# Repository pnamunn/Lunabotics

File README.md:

# NASA Lunabotics 2024 Competition - Team ARES for SDSU

## Distros used:
Using Ubuntu 20.04 LTS on Jetson & Ubuntu 22.04 LTS on laptop.  ROS2 foxy on Jetson & ROS2 humble on laptop.  Different ROS2 versions shouldn't affect their ability to work together over a network.  
Python packages needed for controls:  rclpy, pyserial, sensor_msgs, bitarray  
Python packages needed for modified Vulcan video stream:  cv2, pyrealsense2, flask, numpy  

## Rover telecoms set up:
Ensure laptop & Jetson are both connected to the ARES_WAP

`ros2 run joy joy_node` on laptop to detect Logitech controller

`minicom -D /dev/<arduino_USB_port> -b 500000` on Jetson to serial monitor the Arduino Mega

`python3 serial_joystick.py` on Jetson

<run vulcan video stream on Jetson command>

<connect to appropriate IP address to view video stream on laptop>

## Passwords:
| Device              | Username | Password        |                         |
| :-----------------: | :------: | :-------------: | :---------------------: |
| Laptop              | steui    | WARHAWK         |                         |
| Jetson              | stubert  | S2P@C619        |                         |
| WAP connection      | ARES_WAP | 72878781        |                         |
| WAP config settings | admin    | DoctorShaffar<3 | Website: tplinkwifi.net |

## On Arduino Mega hat:
J17 connects to PB6 (drivetrain R) & PB5(drivetrain L)  
J18 connects to DH3 (exc tilt) & PL4 (depo tilt)  
J19 connects to DH5 (exc height) & PH4 (exc chain)  

## Logitech controller buttons mapping:
| Control        | Use                              |
| -------------: | :------------------------------  |
| Left joystick  | Drivetrain controls              |
| Right joystick | Camera gimble controls           |
| B or X         | Excavation chain fwd or backward |
| Y or A         | Excavation frame move up or down |
| LB or LT       | Depo bin tilt out or in          |
| RB or RT       | Excavation frame tilt out or in  |

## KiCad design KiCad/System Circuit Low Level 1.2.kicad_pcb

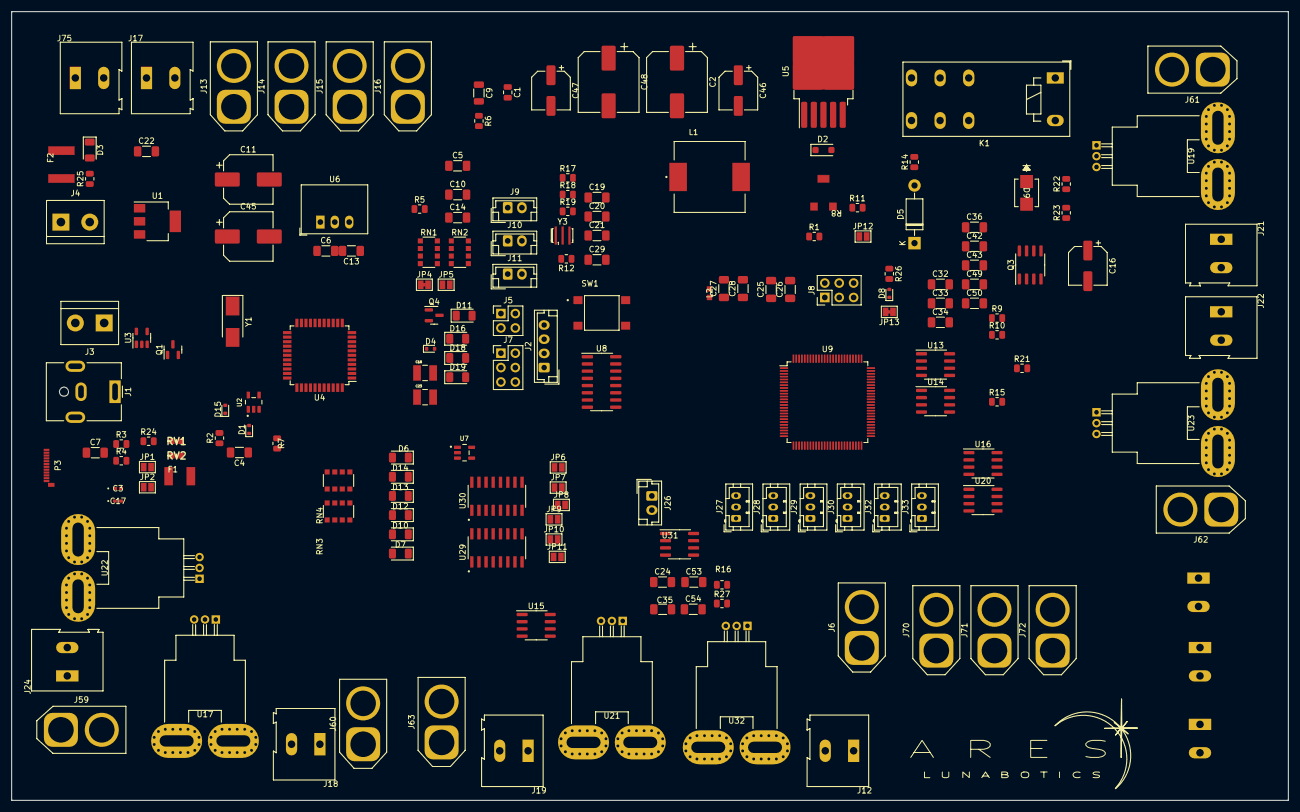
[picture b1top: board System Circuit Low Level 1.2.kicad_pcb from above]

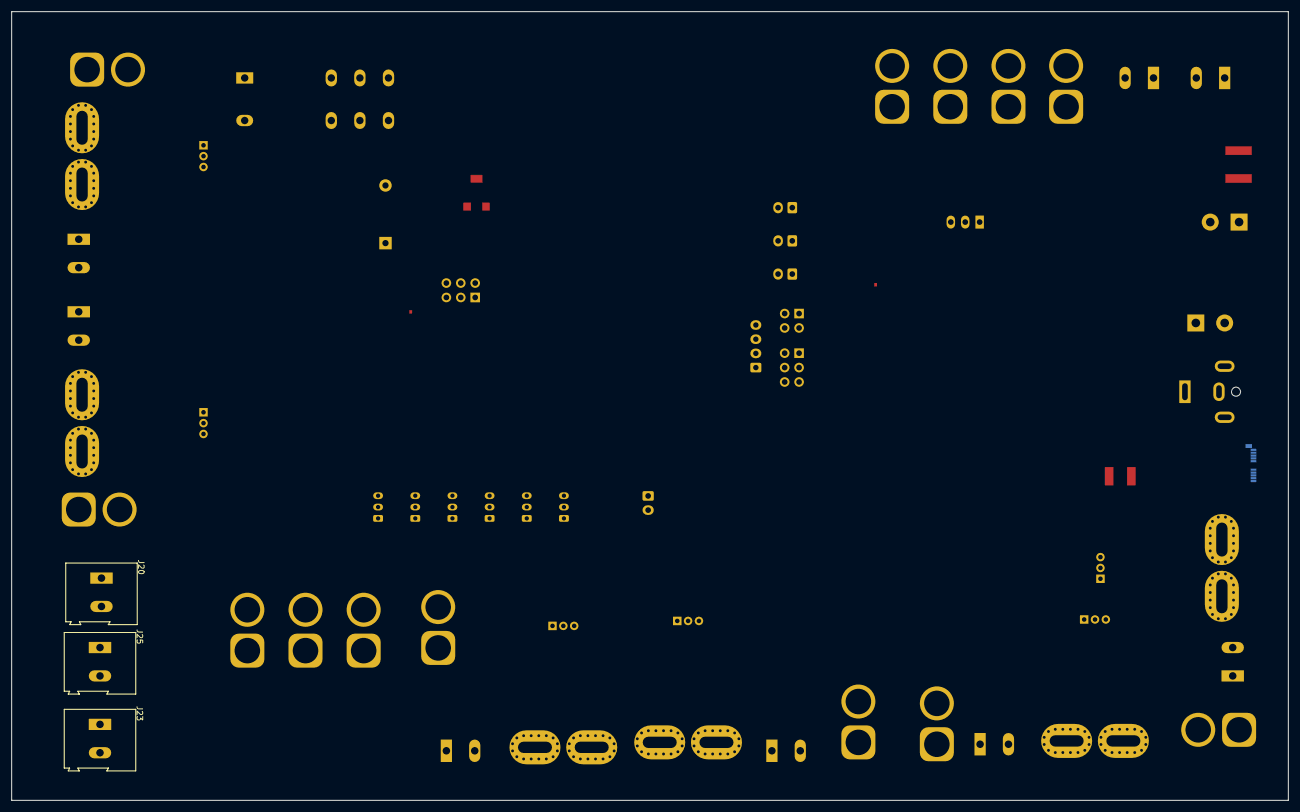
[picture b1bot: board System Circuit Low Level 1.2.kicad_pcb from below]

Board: 2 copper layers, 225.0 x 139.0 mm, 178 parts (3 on the bottom side), 121 nets, no tracks yet.

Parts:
C1: 100n; C_0805_2012Metric
C2, C48: 100u; CP_Elec_10x10.5
C3, C17: 22p; CAP_GCM155_MUR
C4, C5, C7, C10, C13, C14, C19, C21, C22, C24, C25, C26, C27, C28, C29, C32, C33, C34, C35, C36: 0.1u; C_1206_3216Metric_Pad1.33x1.80mm_HandSolder
C6: 0.33u; C_1206_3216Metric_Pad1.33x1.80mm_HandSolder
C9: 330p; C_1206_3216Metric
C11, C45: 47u; CP_Elec_8x10.5
C16, C46, C47: 10u; CP_Elec_6.3x5.8
C18, C23: 10u; CAPC3225X270N
C20: 0.022u; C_1206_3216Metric_Pad1.33x1.80mm_HandSolder
C42, C43, C49, C50, C53, C54: 10n; C_1206_3216Metric_Pad1.33x1.80mm_HandSolder
D1, D4, D8, D15: 1N4148WT; D_SOD-523
D2: MBR1020VL; D_SOD-123F
D3, D6, D7, D10, D11, D12, D13, D14, D16, D18, D19: LED; LED_1206_3216Metric
D5: 1N5819; D_DO-41_SOD81_P10.16mm_Horizontal
D9: 3A100Vstd; SMB_STM
F1: FuseF-MSMF050-2; FuseF-MSMF050-2-sty1
F2: 3A_tr 1.5A_hld Slow Burn; MF-SMDF
J1: Barrel_Jack_Switch; BarrelJack_CUI_PJ-063AH_Horizontal
J2: Conn_01x04; JST_EH_B4B-EH-A_1x04_P2.50mm_Vertical
J3, J4: Screw_Terminal_01x02; TerminalBlock_bornier-2_P5.08mm
J5: Conn_02x02_Odd_Even; PinHeader_2x02_P2.54mm_Vertical
J6, J13, J14, J15, J16, J59, J60, J61, J62, J63, J70, J71, J72: XT-90F-vert; AMASS_XT60-F_1x02_P7.20mm_Vertical
J7, J8: Conn_02x03_Odd_Even; PinHeader_2x03_P2.54mm_Vertical
J9, J10, J11, J26: Conn_01x02; JST_EH_B2B-EH-A_1x02_P2.50mm_Vertical
J12, J17, J18, J19, J20, J21, J22, J23, J24, J25, J75: Screw_Terminal_01x02; TerminalBlock_Altech_AK300-2_P5.00mm
J27, J28, J29, J30, J32, J33: Conn_01x03; JST_PH_B3B-PH-K_1x03_P2.00mm_Vertical
JP1, JP2, JP5, JP6, JP7, JP8, JP9, JP10, JP11, JP12: SolderJumper_2_Open; SolderJumper-2_P1.3mm_Open_Pad1.0x1.5mm
JP4, JP13: SolderJumper_2_Bridged; SolderJumper-2_P1.3mm_Bridged_Pad1.0x1.5mm
K1: RT314A12; Relay_SPDT_Schrack-RT1-16A-FormC_RM5mm
L1: 33u; IND_SRP1265A-330M
L2: 10u; IND_LQM18DN_70_MUR
P3: USB_C_Plug_USB2.0; USB_C_Plug_Molex_105444
Q1: HM2301B; SOT-23
Q3: IRF7403; SOIC-8_3.9x4.9mm_P1.27mm
Q4: S8550D; SOT-23
R1, R22, R23: 100k; R_0805_2012Metric
R2, R7, R26: 10k; R_0805_2012Metric
R3, R12: 1M; R_0805_2012Metric
R4, R24: 22; R_0805_2012Metric
R5: 8.2k; R_0805_2012Metric
R6, R25: 680; R_0805_2012Metric
R8: 5k; 3314G-2-500E
R9, R10, R15, R16, R17, R19, R21, R27: 100; R_0805_2012Metric
R11: 120k; R_0805_2012Metric
R14: 4.7K; R_0805_2012Metric
R18: 20k; R_0805_2012Metric
RN1, RN2, RN3, RN4: 102-1k R Net; R_Array_Convex_4x1206
RV1, RV2: BRNCG063MLC-05E; VARC1608X55N
SW1: SW_Push_Dual; SW_TS07-667-25-BK-100-SMT-TR
U1: LD1117S50TR_SOT223; SOT-223-3_TabPin2
U2, U7: LMV358; SOT95P280X145-5N
U3: LP2985-3.3; SOT-23-5
U4: ATmega32U4-A; TQFP-44_10x10mm_P0.8mm
U5: LM2596S-12; TO-263-5_TabPin3
U6: R-78E9.0-0.5; Converter_DCDC_RECOM_R-78E-0.5_THT
U8: HX711; SOP-16_3.9x9.9mm_P1.27mm
U9: ATmega2560-16A; TQFP-100_14x14mm_P0.5mm
U13, U14, U15, U16, U20, U31: TLC2272; SOIC-8_3.9x4.9mm_P1.27mm
U17, U19, U21, U22, U23, U32: ACS758xCB-050B-PFF; Allegro_CB_PFF
U29, U30: CD4053B; SOIC127P600X175-16N
Y1: Crystal; Crystal_SMD_Abracon_ABM3-2Pin_5.0x3.2mm_HandSoldering
Y3: CSTCE16M0V53-R0; Resonator_SMD_Murata_CSTxExxV-3Pin_3.0x1.1mm_HandSoldering

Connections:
1AX: JP6.2 (B), U16.1 (1OUT), U16.2 (1IN-), U29.12 (A0)
1AY: R21.1, U22.3 (VIOUT), U29.13 (A1)
1BX: JP7.2 (B), U13.1 (1OUT), U13.2 (1IN-), U29.2 (B0)
1BY: R9.1, U17.3 (VIOUT), U29.1 (B1)
1CX: JP8.2 (B), U14.1 (1OUT), U14.2 (1IN-), U29.5 (C0)
1CY: R10.1, U19.3 (VIOUT), U29.3 (C1)
2AX: JP9.2 (B), U20.1 (1OUT), U20.2 (1IN-), U30.12 (A0)
2AY: R15.1, U23.3 (VIOUT), U30.13 (A1)
2BX: JP10.2 (B), U15.1 (1OUT), U15.2 (1IN-), U30.2 (B0), U31.1 (1OUT), U31.2 (1IN-)
2BY: R16.1, R27.1, U21.3 (VIOUT), U30.1 (B1), U32.3 (VIOUT)
2CX: JP11.2 (B), U30.5 (C0)
12V Set-Point: JP12.2 (B), R1.2, U5.4 (FB)
+3V3: U2.2 (-), U3.5 (VOUT)
+5V: C10.1, C11.1, C24.1, C25.1, C26.1, C27.1, C32.1, C33.1, C34.1, C35.1, C36.1, D4.1 (K), J7.2, J8.2, J27.2, J28.2, JP13.1 (A), L2.2, Q1.3 (S), RN2.6, RN2.7, RN2.8, RN3.5, RN3.6, RN3.7, RN3.8, RN4.3, RN4.4, U1.2 (VO), U3.1 (VIN), U3.3 (ON/~OFF), U4.14 (VCC), U4.24 (AVCC), U4.34 (VCC), U4.44 (AVCC), U9.10 (VCC), U9.31 (VCC), U9.61 (VCC), U9.80 (VCC), U13.8 (VDD+), U14.8 (VDD+), U15.8 (VDD+), U16.8 (VDD+), U17.1 (VCC), U19.1 (VCC), U20.8 (VDD+), U21.1 (VCC), U22.1 (VCC), U23.1 (VCC), U29.16 (VDD), U30.16 (VDD), U31.8 (VDD+), U32.1 (VCC)
+9V: C13.1, J29.1, J30.1, J32.1, J33.1, U6.3 (OUT)
+12V: C1.1, C2.1, C6.1, C9.1, C46.1, C47.1, C48.1, D3.2 (A), L1.2, R11.2, U6.1 (IN)
+S: C19.1, J2.3, R17.2
-E PROX: C1.2, C2.2, C3.1, C4.2, C6.2, C7.2, C10.2, C11.2, C13.2, C14.1, C16.2, C17.1, C18.2, C20.2, C21.1, C22.1, C23.2, C24.2, C25.2, C26.2, C27.2, C28.2, C32.2, C33.2, C34.2, C35.2, C36.2, C42.2, C43.2, C45.2, C46.2, C47.2, C48.2, C49.2, C50.2, C53.2, C54.2, D2.2 (A), D6.1 (K), D7.1 (K), D10.1 (K), D11.1 (K), D12.1 (K), D13.1 (K), D14.1 (K), D19.1 (K), J1.2, J2.2, J4.2, J7.6, J8.6, J17.1, J27.3, J28.3, J29.3, J30.3, J32.3, J33.3, JP1.1 (A), JP1.2 (B), JP2.1 (A), JP5.2 (B), Q3.1 (S), Q3.2 (S), Q3.3 (S), R1.1, R5.1, R6.2, R7.1, R23.2, R25.1, RN1.1, SW1.1, SW1.3, U1.1 (GND), U3.2 (GND), U4.5 (UGND), U4.15 (GND), U4.23 (GND), U4.35 (GND), U4.43 (GND), U5.3 (GND), U5.5 (~ON/OFF), U6.2 (GND), U8.5 (AGND), U8.9 (INB-), U8.10 (INB+), U8.14 (XI), U8.15 (RATE), U9.11 (GND), U9.32 (GND), U9.62 (GND), U9.81 (GND), U9.99 (GND), U13.4 (GND), U14.4 (GND), U15.4 (GND), U16.4 (GND), U17.2 (GND), U19.2 (GND), U20.4 (GND), U21.2 (GND), U22.2 (GND), U23.2 (GND), U29.7 (VEE), U29.8 (VSS), U30.7 (VEE), U30.8 (VSS), U31.4 (GND), U32.2 (GND)
-S: C19.2, J2.4, R19.2
E+: C18.1, J2.1, Q4.3 (C), R18.2, U8.3 (AVDD)
E-SWTCH IN: D9.1 (K), J17.2, J75.1, K1.11, K1.A2, R14.1, R22.1
MISO: J8.1, U9.22 (PB3)
MOSI: J8.4, U9.21 (PB2)
unnamed: C9.2, R6.1
unnamed: D1.2 (A), J3.1
unnamed: D2.1 (K), L1.1, U5.2 (OUT)
unnamed: D3.1 (K), R25.2
unnamed: D5.2 (A), K1.14, R14.2
unnamed: D5.1 (K), U5.1 (VIN)
unnamed: D6.2 (A), RN3.1
unnamed: D7.2 (A), RN3.2
unnamed: D8.1 (K), JP13.2 (B), R26.1
unnamed: D9.2 (A), K1.A1, Q3.5 (D), Q3.6 (D), Q3.7 (D), Q3.8 (D)
unnamed: D10.2 (A), RN3.3
unnamed: D11.2 (A), RN2.4
unnamed: D12.2 (A), RN3.4
unnamed: D13.2 (A), RN4.5
unnamed: D14.2 (A), RN4.6
unnamed: D15.2 (A), J1.1
unnamed: D16.2 (A), RN2.3
unnamed: D16.1 (K), U4.22 (PD5)
unnamed: D18.2 (A), RN2.2
unnamed: D18.1 (K), U4.25 (PD4)
unnamed: D19.2 (A), RN2.1
unnamed: P3.A4 (VBUS), P3.A9 (VBUS), P3.B4 (VBUS), P3.B9 (VBUS)
unnamed: J5.1, U4.28 (PB4)
unnamed: J5.2, U4.30 (PB6)
unnamed: J5.3, U4.29 (PB5)
unnamed: J5.4, U4.12 (PB7)
unnamed: J7.1, U4.11 (PB3)
unnamed: J7.3, U4.9 (PB1)
unnamed: J7.4, U4.10 (PB2)
unnamed: J12.2, U32.4 (IP+)
unnamed: J18.2, U17.4 (IP+)
unnamed: J19.2, U21.4 (IP+)
unnamed: J21.2, U19.4 (IP+)
unnamed: J22.2, U23.4 (IP+)
unnamed: J24.2, U22.4 (IP+)
unnamed: J27.1, U7.3 (+), U9.26 (PB7)
unnamed: J29.2, U9.46 (PD3)
unnamed: J30.2, U9.6 (PE4)
unnamed: J32.2, U9.45 (PD2)
unnamed: J33.2, U9.7 (PE5)
unnamed: JP2.2 (B), U4.42 (AREF)
unnamed: C20.1, JP4.1 (A)
unnamed: C14.2, JP5.1 (A), U9.98 (AREF)
unnamed: JP6.1 (A), U9.77 (PA1), U29.14 (A)
unnamed: JP7.1 (A), U9.76 (PA2), U29.15 (B)
unnamed: JP8.1 (A), U9.75 (PA3), U29.4 (C)
unnamed: JP9.1 (A), U9.74 (PA4), U30.14 (A)
unnamed: JP10.1 (A), U9.73 (PA5), U30.15 (B)
unnamed: JP11.1 (A), U9.72 (PA6), U30.4 (C)
unnamed: JP12.1 (A), R11.1
unnamed: P3.A6 (D+), R4.1, RV2.1
unnamed: P3.A7 (D-), R24.1, RV1.1
unnamed: P3.A1 (GND), P3.A12 (GND), P3.B1 (GND), P3.B12 (GND)
unnamed: P3.S1 (SHIELD), RV1.2, RV2.2
unnamed: C7.1, Q1.1 (D), U4.2 (UVCC), U4.7 (VBUS)
unnamed: Q1.2 (G), U2.1
unnamed: C16.1, Q3.4 (G), R22.2, R23.1
unnamed: Q4.2 (B), U8.2 (BASE)
unnamed: C23.1, Q4.1 (E), U8.1 (VSUP), U8.16 (DVDD)
unnamed: C4.1, R2.1, R7.2, U2.3 (+)
unnamed: R24.2, U4.4 (D+)
unnamed: R4.2, U4.3 (D-)
unnamed: RN1.6, U4.20 (PD2)
unnamed: RN1.7, U4.21 (PD3)
unnamed: C5.1, RN1.8, U4.27 (PD7)
unnamed: C3.2, R3.1, U4.17 (XTAL1), Y1.2
unnamed: C17.2, R3.2, U4.16 (XTAL2), Y1.1
unnamed: RN2.5, U7.1, U7.2 (-)
unnamed: U8.12 (DOUT), U9.41 (PL6)
unnamed: R17.1, U8.8 (INA+)
unnamed: R19.1, U8.7 (INA-)
unnamed: U8.11 (PD_SCK), U9.42 (PL7)
unnamed: C21.2, U8.6 (VBG)
unnamed: R5.2, R18.1, U8.4 (VFB)
unnamed: C28.1, L2.1, U9.100 (AVCC)
unnamed: RN1.2, U9.2 (PE0)
unnamed: RN1.3, U9.3 (PE1)
unnamed: R12.2, U9.34 (XTAL1), Y3.1
unnamed: R12.1, U9.33 (XTAL2), Y3.2
unnamed: C43.1, R9.2, U13.3 (1IN+)
unnamed: C49.1, R10.2, U14.3 (1IN+)
unnamed: C53.1, R16.2, U15.3 (1IN+)
unnamed: C42.1, R21.2, U16.3 (1IN+)
unnamed: C50.1, R15.2, U20.3 (1IN+)
unnamed: C54.1, R27.2, U31.3 (1IN+)
RESET1: C5.2, D8.2 (A), J8.5, JP4.2 (B), R26.2, SW1.2, SW1.4, U9.30 (~RESET)
RESET2: D4.2 (A), J7.5, U4.13 (~RESET)
SCK: J8.3, U9.20 (PB1)
Sig - CAM Y: J28.1, U9.5 (PE3)
Sig - DEPO BIN TILT: J26.2, U9.25 (PB6)
Sig - EXC ASC/DSC: J26.1, U9.24 (PB5)
Sig - EXCV TILT: J11.2, U9.17 (PH5)
Sig - Ex Sprckt: J11.1, U9.16 (PH4)
Sig - L1: J9.1, U9.38 (PL3)
Sig - L2: J9.2, U9.39 (PL4)
Sig - R1: J10.1, U9.40 (PL5)
Sig - R2: J10.2, U9.15 (PH3)
V-IN: C22.2, C45.1, D1.1 (K), D15.1 (K), R2.2, U1.3 (VI)

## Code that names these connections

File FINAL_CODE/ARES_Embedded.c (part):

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
#define TOP_40HZ	39999

#define DRIVE_L		OCR1A	// Arduino pin 11, PB5
#define DRIVE_R		OCR1B	// pin 12, PB6
// #define SERVO_L		OCR1C	// pin 13, PB7
// #define SERVO_R		OCR3A	// pin 5, PE3
#define DEPO_TILT	OCR5B	// pin 45, PL4
#define EXC_TILT	OCR4A	// pin 6, PH3
#define EXC_CHAIN	OCR4B	// pin 7, PH4
#define EXC_HEIGHT	OCR4C	// pin 8, PH5

volatile	uint8_t DIRencoder = 0X00;
volatile	char	key		   =    0;
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
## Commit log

2023-10-20 Create test.txt
    test push
2023-10-20 Create main.c
    This program generates a signal to drive TB6612FNG H-Bridge. w/e drives motors lolz
2023-10-25 Create CAD
2023-11-06 Rough Design
2023-11-06 Create UART HBridge Driver.c
    This is a mess. Program works w Putty, Terra Term- Interrupt driven... w/e. still needs a watch dog mechanism
2023-11-06 Create HADES
    HADES CAD models
2023-11-06 added HADES CAD
    * HADES CAD files
2023-11-08 Added distros & CLI help to README
2023-11-08 typo
2023-11-08 for a 1ft wheel with 18 grousers, bad screws
2023-11-10 Wield Excavation
2023-11-13 Create gamepad_publisher.py
    skeleton code for gamepad publisher node
2023-11-17 stuff
2023-11-20 Delete gamepad_publisher.py
    not needed bc joy acts as publisher
2023-11-20 Create gamepad_launch.py
    launches 2 nodes, pubber & subber for gamepad
2023-11-20 Create minimal_pubber.py
    example code for coding a pubber node
2023-11-20 Create serial_blink.py
    Python script that can send serial data to an Arduino that is expecting that data
2023-11-20 Update gamepad_launch.py
    fixed typos
2023-11-25 Create switch_networks.sh
    Has error when running on ssh connection that disconnects
2023-11-25 small updates
2023-11-25 small typos fixed
2023-11-25 Create serial_gamepad.py
    No serial comms yet, only a subber that grabs the button data being published by /joy
2023-11-25 found & fixed errors encountered when trying to run on Stubot
2023-11-27 debugged .py file on StuBot, python3 file now runs correctly (logging gamepad presses), did not try ros2 running it
2023-11-27 Drivetrain & linear actuators controls work via Dpad & bumpers & trigger
2023-11-27 added if statements to make the Zyn bot drive forward & backward
2023-11-27 code for drivetrain & excavator linear actuators added
2023-11-28 commented out code
    strange behavior in last version, commented out code
2023-11-28 added encoding and changed axes[] element
2023-11-29 Create test.txt
    testing
2023-12-02 Create StemEngagement.ino
    WIP Code or Stem Engagement drive train - Jonathan
2023-12-05 Corrected if-statements for DPad control and linear actuators
2023-12-08 File reorganization
2023-12-12 changed to launch serial_gamepad node
2023-12-12 File organization for stem_engagement
2023-12-12 schematic with L298N motor driver
2023-12-12 file organization
    Put .ino file in a dir of the same name so that the .ino file can be opened by the Arduino IDE
2023-12-15 Update
    State Machine removed, faster. Pullup enable, less dumb. = def not |=, syntax killer of champions
2023-12-16 Create gscam.launch.py
    launches gstreamer gscam_node
2023-12-16 fixed boolean errors
2023-12-23 added zeroing of loadcell in loadcell_offset function
2024-01-08 meh
    some ft prints are customized
2024-01-26 starting to add joystick controls
    Unfinished
2024-01-31 Update serial_gamepad.py
    starting to do joystick code
2024-01-31 Update serial_gamepad.py
    cont. joystick control
2024-02-01 Added single stick arcade drive for joystick
    untested code
2024-02-03 added joystick control with serial commands. Still needs to be verified
2024-02-08 add comments to describe pipeline
2024-02-09 arcade drive math + word sending
2024-02-09 decided on normalizing procedure
2024-02-09 UART Rx for receiving 16 bit values (joystick values)
2024-02-09 added joystick in deadzone case
2024-02-09 testing out gscam on WARHAWK webcam
2024-02-13 comments, refactoring, error message printing
2024-02-14 on msg_handler()
    defined message_type addr values, wrote TODOs
2024-02-14 normalize & send motor values to Arduino
    normalize motor values in prep to send to Arduino, send motor values in accordance to C msg_handler() protocol
2024-02-16 added curr & last value monitoring for joystick deadzone
2024-02-16 added UART0_RX ISR
2024-02-16 changed py code to send werds in right order
2024-02-16 Create ASC758 driver 16.c
    This right justified program uses breadth of ADC to read 2 current sensors alternating. Where 15 integers of range is thin for change in current (510-525), it's better than the (127-131) for a curren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
2024-02-20 added serial prints for testing
    trying to solve soft reset problem
2024-02-21 case 2 update
    msg_handler() should now be working correctly for case 2
2024-02-21 current sensor code attempt
2024-02-29 Fixed bytes & order of sending
2024-02-29 fixed wrong deadzone vals
2024-02-29 no more +'p' character stuff
    some tiny fixes
2024-02-29 testing out streaming, not working yet
2024-03-01 Added Vulcan's camera stream code
2024-03-02 serial formatting
2024-03-04 printing in binary
2024-03-04 implementing acks & nacks
2024-03-04 acks & nacks
2024-03-06 Upload initial ROS2 current sensor code.
2024-03-06 changed baud to 500000
2024-03-06 sends bytes correctly, baud change
2024-03-06 Update CurrensSensorROSSubber.py
    Fixed upload
2024-03-07 Root Cause
    Segregated, per data sheet async require 2 U2X0, why factors of double the BAUD worked, increase the divider to return to 115200 BAUD, hard reset on the Arduino will reliably flush UDR0 register yiel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
2024-03-07 Update CurrensSensorROSPublisher.py
    Simple bug fixes
2024-03-07 Update CurrensSensorROSSubber.py
    Simple bug fixes
2024-03-07 added the camera stuffs
2024-03-12 removed delays & lessened deadzone
2024-03-13 watchdog does not interrupt controls
2024-03-13 started button code
2024-03-14 Updated Current Sensor ROS code
2024-03-15 Update CurrensSensorROSSubber.py
    Fixed the dumb file
2024-03-15 Update CurrensSensorROSSubber.py
    Debugged Current Sensor so it now compiles. Also noticed that the file name has a typo in it ;(
2024-03-15 Update CurrensSensorROSPublisher.py
    Fixed the callback. Code now comiles
2024-03-19 more efficient comparision in callback
2024-03-22 Update current_sensor.c
    Switches between ADC2 and ADC3, new sensitivity with amplifier
2024-03-22 created button control code
    also changed init_DIR() to 2 separate functs
2024-03-22 reworked Rx ISR logic
2024-03-22 revert: comparision put back in send_dut_vals()"
2024-03-23 camera stuffs
2024-03-24 Update CurrensSensorROSPublisher.py
    Worked on Serial connection
2024-03-24 Create current_sensor_mega
2024-03-24 Rename current_sensor_mega to current_sensor_mega.c
2024-03-25 delay between Txs
2024-03-25 current sensor pubber integration started
2024-03-26 mistake fix, sends deadzone motor vals now
2024-03-27 cad only branch
2024-03-28 PWM val fixed; depo bin tilt pin changed
2024-04-03 mistake found, sent bytes twice ???
2024-04-03 Update current_sensor.c for Arduino Mega
2024-04-03 ARES_Embedded now uses .h files
    for code organization
2024-04-03 receives and prints data coming from Arduino
2024-04-03 trying UDP Gstreamer
2024-04-03 changed read() timeout & bitwise op on Python's 32 bit int
    also made low & high motor vals & with 32 bits for Python's 32 bit int data type
2024-04-06 Put watchdog reset in msg_handler & added double buttons
    also changes some LA speeds to half speed
2024-04-14 Split ARES Embedded.c into main & header files
2024-04-14 started priority scheduling & current sensor polling
2024-04-16 added Arduino hat help
2024-04-16 reorganize & wrote .md readme
2024-04-16 reorganize files
2024-04-16 passwords (so sue me, you need the physical things anyway)
2024-04-16 Revert "Squashed commit of the following:"
    This reverts commit 0ca7ddda6cd4e5faa59e093bc2a898d7b326d731.
2024-04-16 exponential drive equation
2024-04-18 working threshold alerts for current sensors
2024-04-18 Create CAM_srvo.c
    Rough draft of motors on camera
2024-04-18 Embedded Atmel project solution
2024-05-02 Initializes with rover drivetrain stopped
2024-05-02 add gimble joystick controls
2024-05-03 right joystick working for gimble (but code ugly)
2024-05-03 support gimble servos
2024-05-03 added CONOPs info
    bootup instructions, passwords, and Logitech controller mappings
2024-05-04 add exponential arcade drive
2024-05-04 Gimble servos init correctly
2024-05-05 linear & exponential code files
2024-05-05 ARES_Embedded w load cell code
2024-05-15 Reapply "Squashed commit of the following:"
    This reverts commit 8523155ff6cc300d5b31a5990088b6d4260c5c95.
2024-06-06 Add header documentation
2024-06-06 add final comp serial code
2024-06-06 consolidation of code
2024-06-06 consolidated arcade drive functions
2024-06-06 reorganize
2024-06-06 add button mappings
2024-06-06 organization
2024-06-06 added documentation links
2024-06-06 readme doc
2024-09-05 repo organization
2024-11-19 oops unpushed changes living rent free
